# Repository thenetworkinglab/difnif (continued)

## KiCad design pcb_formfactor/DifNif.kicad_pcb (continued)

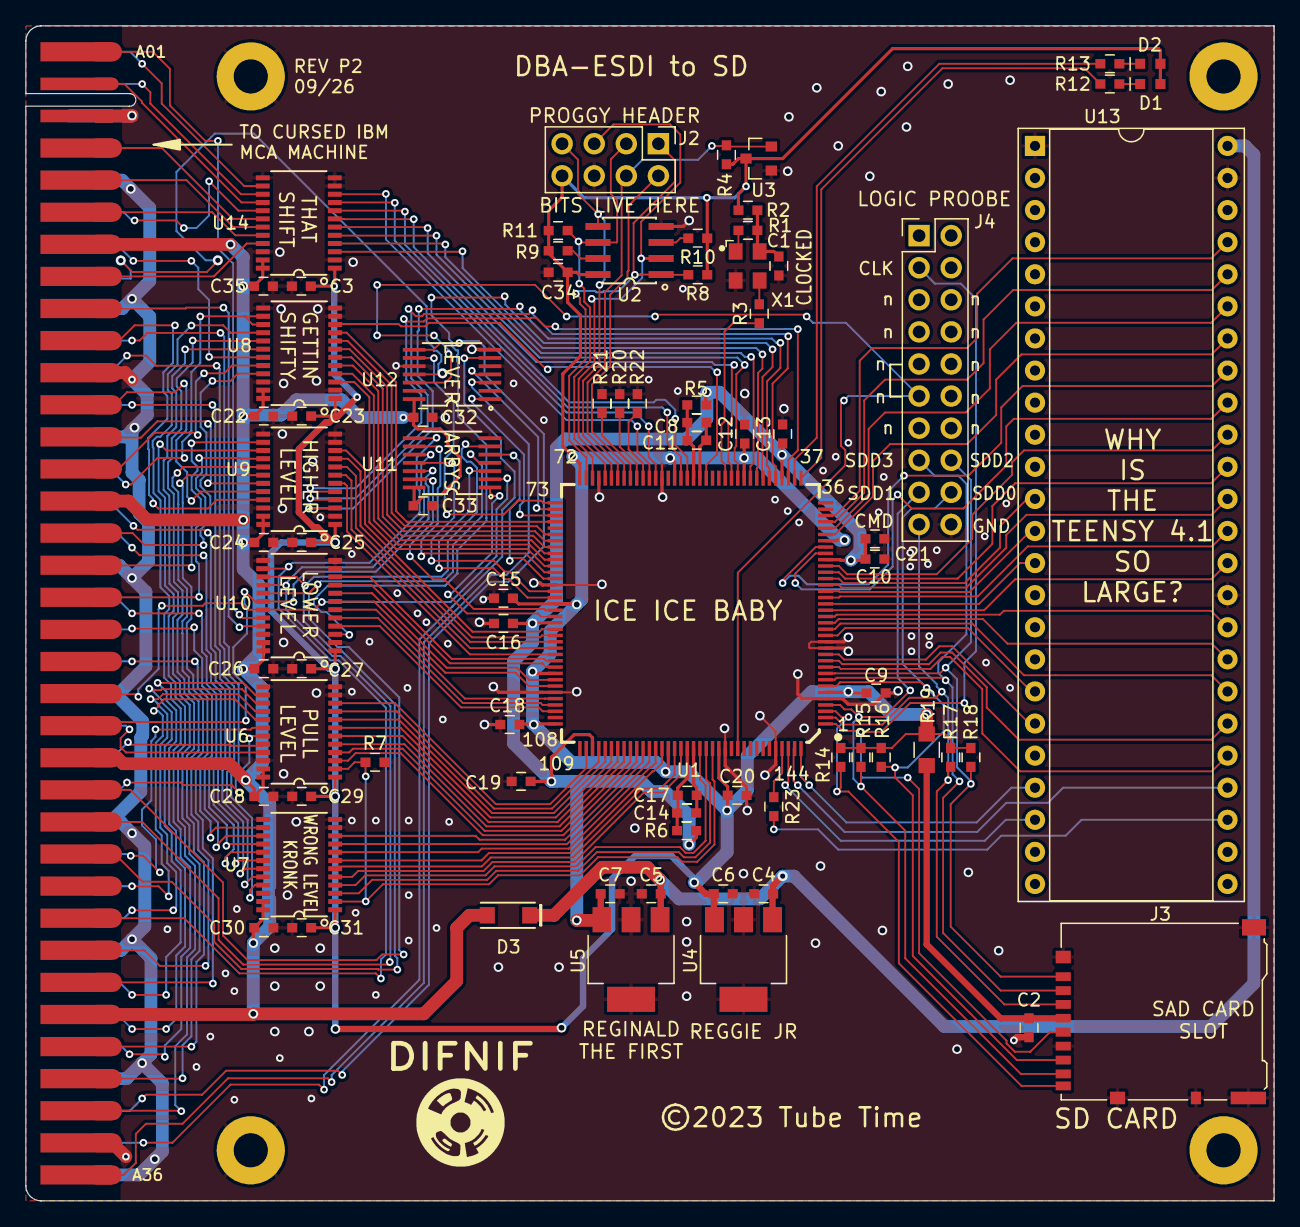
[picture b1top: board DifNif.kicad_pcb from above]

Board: 2 copper layers, 98.8 x 93.0 mm, 84 parts (0 on the bottom side), 172 nets.

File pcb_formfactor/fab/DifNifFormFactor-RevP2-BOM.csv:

Item,Qty,Designators,Manufacturer,Manufacturer Part Number,Description,Value,Footprint,Type,Fitted by,Mouser,Notes
1,13,C1 C2 C9 C10 C11 C12 C13 C15 C16 C17 C18 C19 C34,TDK,CGA3E1X7R1C105AC,Capacitor 1u 0603,1u,CAPC1608X100,SMD,Assembler,810-CGA3E1X7R1C105AC,
2,14,C3 C22 C23 C24 C25 C26 C27 C28 C29 C30 C31 C32 C33 C35,Samsung Electro-Mechanics,CL10B104KB8NNNC,Capacitor 0.1uF 0603,0.1uF,CAPC1608X100,SMD,Assembler,,Any 0.1 uF X7R 0603 rated 16 V or more is fine
3,8,C4 C5 C6 C7 C8 C14 C20 C21,Samsung Electro-Mechanics,CL10A475KP8NNNC,Capacitor 4.7u 0603,4.7u,CAPC1608X100,SMD,Assembler,187-CL10A475KP8NNNC,
4,2,D1 D2,,,"LED, 0603",LED,LEDM1608X50,SMD,Assembler,,Any 0603 LED (e.g. green); 470 ohm from 3.3 V
5,1,D3,Nexperia,PMEG10010ELRX,"Schottky diode 1 A 100 V, SOD-123F",PMEG10010ELR,SOD3716X117,SMD,Assembler,771-PMEG10010ELRX,
6,1,J3,Hirose,DM3AT-SF-PEJM5(40),microSD socket,SDCARD_DM3AT-SF-PEJM5,microSD_HC_Hirose_DM3AT-SF-PEJM5,SMD,Assembler,798-DM3AT-SF-PEJM540,"Check: Mouser code ends in 40, Hirose's packaging variant"
7,6,R1 R4 R8 R9 R10 R11,Yageo,RC0603FR-0710KL,Resistor 10K 0603,10K,RESC1608X55,SMD,Assembler,603-RC0603FR-0710KL,
8,6,R2 R3 R20 R21 R22 R23,Yageo,RC0603FR-0710RL,Resistor 10 0603,10,RESC1608X55,SMD,Assembler,603-RC0603FR-0710RL,
9,2,R5 R6,Yageo,RC0603FR-07100RL,Resistor 100 0603,100,RESC1608X55,SMD,Assembler,603-RC0603FR-07100RL,
10,1,R7,Yageo,RC0603FR-071KL,Resistor 1K 0603,1K,RESC1608X55,SMD,Assembler,603-RC0603FR-071KL,
11,2,R12 R13,Yageo,RC0603FR-07470RL,Resistor 470 0603,470,RESC1608X55,SMD,Assembler,603-RC0603FR-07470RL,
12,5,R14 R15 R16 R17 R18,Yageo,RC0603FR-0747KL,Resistor 47K 0603,47K,RESC1608X55,SMD,Assembler,603-RC0603FR-0747KL,
13,1,R19,Yageo,RC0805FR-070RL,Resistor 0 0805,0,RESC2012X55,SMD,Assembler,603-RC0805FR-070RL,
14,1,U1,Lattice Semiconductor,ICE40HX4K-TQ144,"FPGA, iCE40 HX4K, TQFP-144",ICE40HX4K-TQ144,TSQFP50P2200X2200X160-144,SMD,Assembler,842-ICE40HX4K-TQ144,
15,1,U2,Microchip Technology,SST26VF080A-104I/SN,"SPI flash 8 Mbit, SOIC-8 (FPGA configuration)",SST26VF080A-104I/SN,SOP127P620X175-8,SMD,Assembler,579-26VF080A-104I/SN,
16,1,U3,Diodes Incorporated,APX803S00-29SA-7,"Reset supervisor 2.93 V, SOT-23",APX803S00-29SA-7,SOT95P230X117-3,SMD,Assembler,621-APX803S00-29SA-7,
17,1,U4,Diodes Incorporated,AP2114HA-3.3TRG1,"LDO 3.3 V, SOT-223",AP2114HA-3.3,SOT230P700X170-3,SMD,Assembler,621-AP2114HA-3.3TRG1,
18,1,U5,Diodes Incorporated,AP2114HA-1.2TRG1,"LDO 1.2 V, SOT-223",AP2114HA-1.2,SOT230P700X170-3,SMD,Assembler,621-AP2114HA-1.2TRG1,
19,6,U6 U7 U8 U9 U10 U14,Texas Instruments,SN74LVC8T245PWR,"Dual-supply octal transceiver, TSSOP-24",74LVC8T245,TSOP65P640X120-24,SMD,Assembler,595-SN74LVC8T245PWR,
20,1,U11,Toshiba,74LCX07FT,"Hex open-drain buffer, TSSOP-14",74LCX07,TSOP65P640X110-14,SMD,Assembler,757-74LCX07FTAE,Check: Mouser code adds a packaging suffix (AE)
21,1,U12,Toshiba,74VHCT125AFT,"Quad tri-state buffer, TSSOP-14",74VHCT125,TSOP65P640X110-14,SMD,Assembler,757-74VHCT125AFT,
22,1,X1,ECS Inc.,ECS-2333-100-BN-TR,Oscillator 10 MHz,ASE-xxxMHz,XTAL320X250X120-4,SMD,Assembler,520-ECS-2333-100-BNT,"Check: 10 MHz 3.3 V oscillator, 3.2 x 2.5 mm; Mouser code drops the -TR punctuation"
23,1,J2,,,"2x4 pin header, 2.54 mm",PROG,PinHeader_2x04_P2.54mm_Vertical,THT,Customer,,FPGA flash programming header
24,1,J4,,,"2x10 pin header, 2.54 mm",HPLA_PORT,PinHeader_2x10_P2.54mm_Vertical,THT,Customer,,Logic analyzer header (HP pod)
25,1,U13,,,"2x 1x24 female socket strips, 2.54 mm, rows 15.24 mm apart",Teensy4_1,DIP-48_W15.24mm_Socket,THT,Customer,,Socket for the Teensy 4.1 (Teensy fitted separately)

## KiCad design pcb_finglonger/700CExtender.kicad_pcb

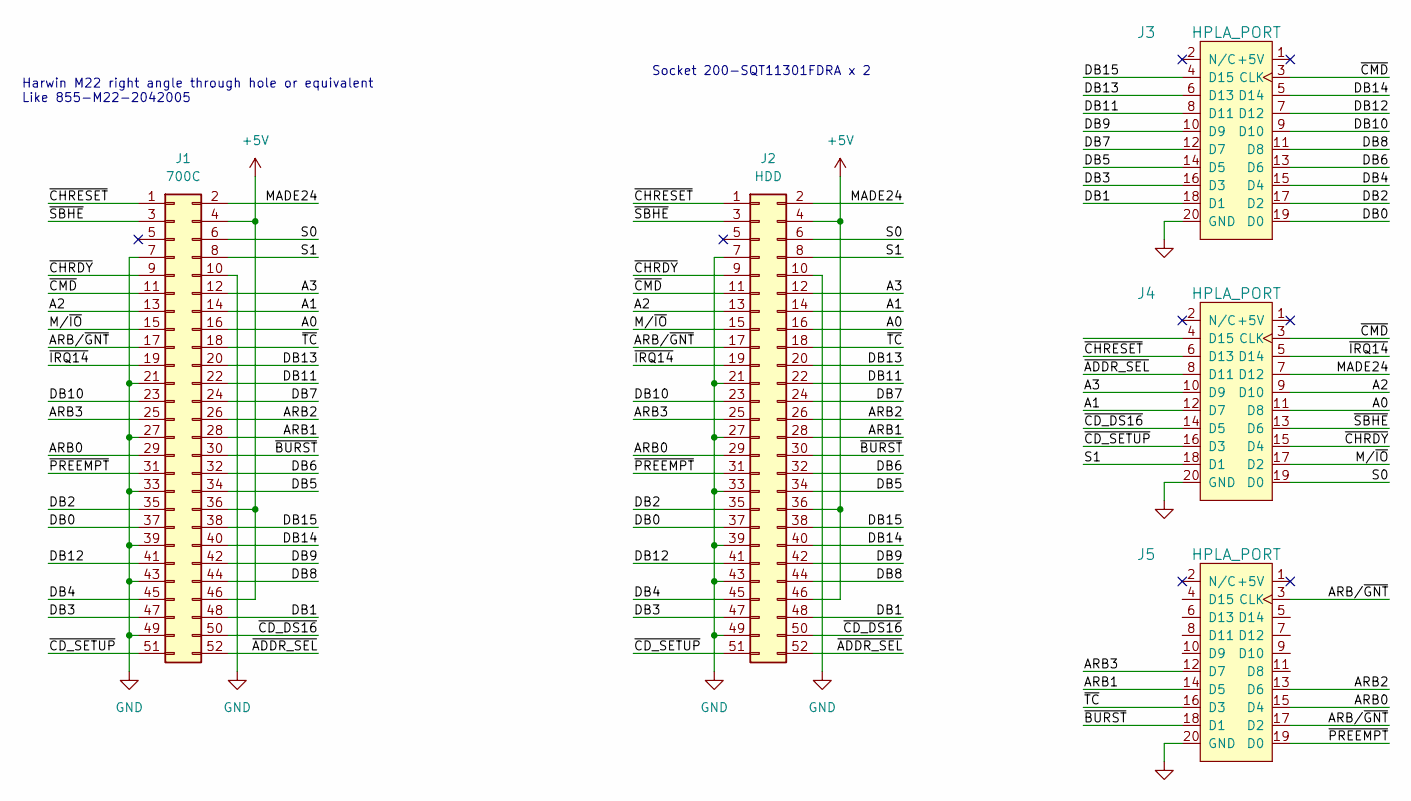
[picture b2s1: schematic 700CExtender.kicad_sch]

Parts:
J1: 700C; PinHeader_2x26_P2.00mm_Vertical
J2: HDD; PinSocket_2x26_P2.00mm_Vertical
J3, J4, J5: HPLA_PORT; PinHeader_2x10_P2.54mm_Vertical

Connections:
+5V: J1.4, J1.36, J1.46, J2.4, J2.36, J2.46
/A0: J1.16, J2.16, J4.11 (D8)
/A1: J1.14, J2.14, J4.12 (D7)
/A2: J1.13, J2.13, J4.9 (D10)
/A3: J1.12, J2.12, J4.10 (D9)
/ARB0: J1.29, J2.29, J5.15 (D4)
/ARB1: J1.28, J2.28, J5.14 (D5)
/ARB2: J1.26, J2.26, J5.13 (D6)
/ARB3: J1.25, J2.25, J5.12 (D7)
/ARB/~GNT: J1.17, J2.17, J5.3 (CLK), J5.17 (D2)
/DB0: J1.37, J2.37, J3.19 (D0)
/DB1: J1.48, J2.48, J3.18 (D1)
/DB2: J1.35, J2.35, J3.17 (D2)
/DB3: J1.47, J2.47, J3.16 (D3)
/DB4: J1.45, J2.45, J3.15 (D4)
/DB5: J1.34, J2.34, J3.14 (D5)
/DB6: J1.32, J2.32, J3.13 (D6)
/DB7: J1.24, J2.24, J3.12 (D7)
/DB8: J1.44, J2.44, J3.11 (D8)
/DB9: J1.42, J2.42, J3.10 (D9)
/DB10: J1.23, J2.23, J3.9 (D10)
/DB11: J1.22, J2.22, J3.8 (D11)
/DB12: J1.41, J2.41, J3.7 (D12)
/DB13: J1.20, J2.20, J3.6 (D13)
/DB14: J1.40, J2.40, J3.5 (D14)
/DB15: J1.38, J2.38, J3.4 (D15)
/MADE24: J1.2, J2.2, J4.7 (D12)
/M/~IO: J1.15, J2.15, J4.17 (D2)
/S0: J1.6, J2.6, J4.19 (D0)
/S1: J1.8, J2.8, J4.18 (D1)
/~ADDR_SEL: J1.52, J2.52, J4.8 (D11)
/~BURST: J1.30, J2.30, J5.18 (D1)
/~CD_DS16: J1.50, J2.50, J4.14 (D5)
/~CD_SETUP: J1.51, J2.51, J4.16 (D3)
/~CHRDY: J1.9, J2.9, J4.15 (D4)
/~CHRESET: J1.1, J2.1, J4.6 (D13)
/~CMD: J1.11, J2.11, J3.3 (CLK), J4.3 (CLK)
/~IRQ14: J1.19, J2.19, J4.5 (D14)
/~PREEMPT: J1.31, J2.31, J5.19 (D0)
/~SBHE: J1.3, J2.3, J4.13 (D6)
/~TC: J1.18, J2.18, J5.16 (D3)
GND: J1.7, J1.10, J1.21, J1.27, J1.33, J1.39, J1.43, J1.49, J2.7, J2.10, J2.21, J2.27, J2.33, J2.39, J2.43, J2.49, J3.20 (GND), J4.20 (GND), J5.20 (GND)

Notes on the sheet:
Harwin M22 right angle through hole or equivalent Like 855-M22-2042005
Socket 200-SQT11301FDRA x 2

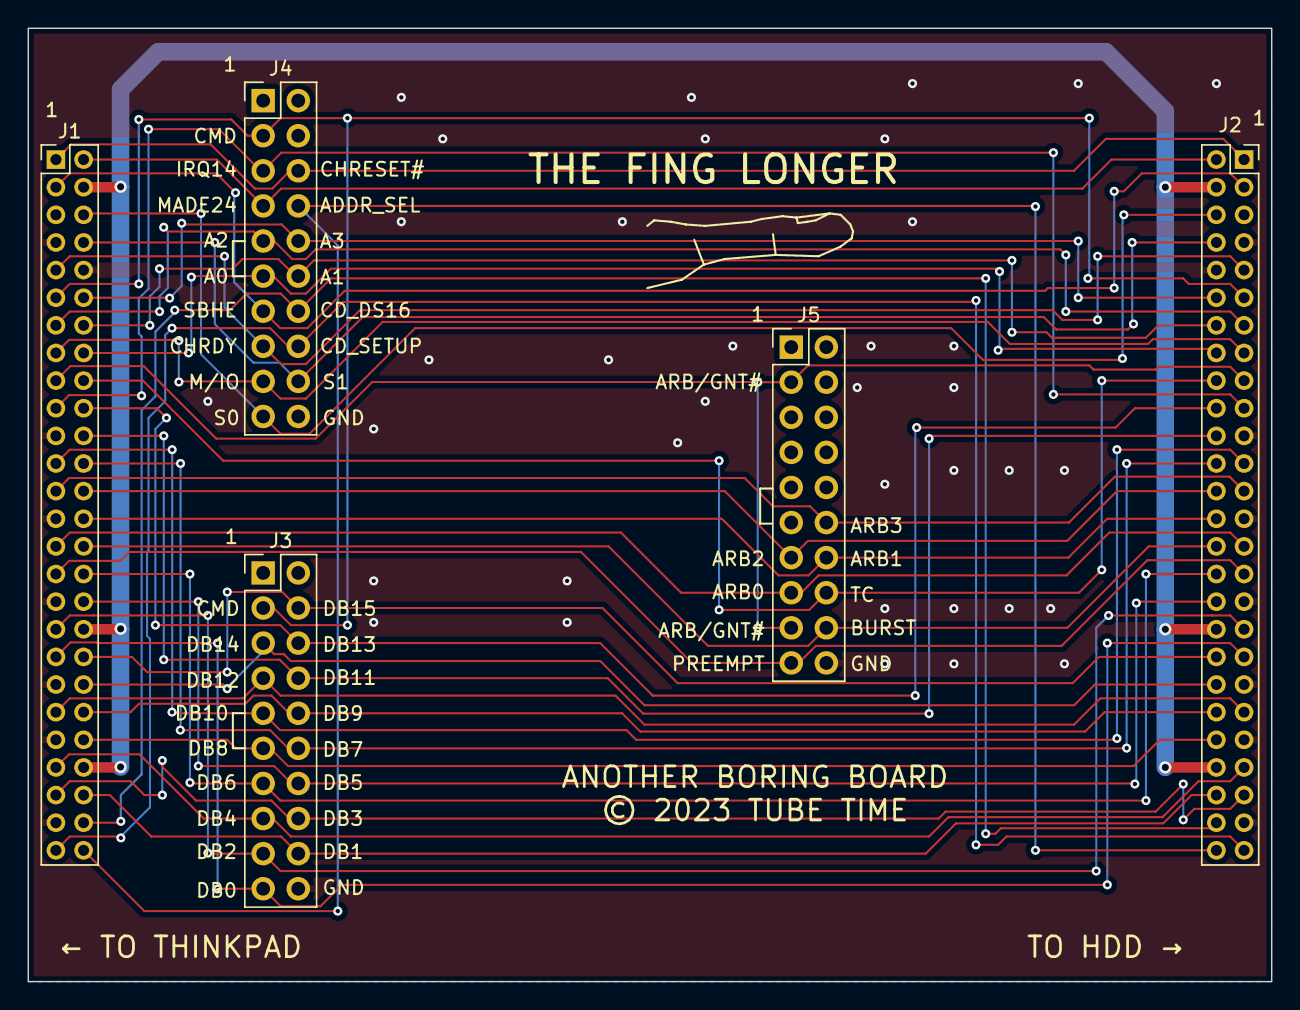
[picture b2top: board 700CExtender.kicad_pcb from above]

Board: 2 copper layers, 90.0 x 69.0 mm, 5 parts (0 on the bottom side), 42 nets.

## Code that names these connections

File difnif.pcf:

### icetest

### Copyright (c) 2021 Eric Schlaepfer
### This work is licensed under the Creative Commons Attribution-ShareAlike 4.0
### International License. To view a copy of this license, visit
### http://creativecommons.org/license/by-sa/4.0/ or send a letter to Creative
### Commons, PO Box 1866, Mountain View, CA 94042, USA.

### Clock
set_io clk_10m      49

### Micro Channel bus
set_io chreset_l    52 # Probably not actually chreset_l!

set_io cd_ds16_l    73
set_io irq14_l      74
set_io cd_chrdy_l   75
set_io chreset      76
set_io sbhe_l       78
set_io s0_w_l       79
set_io s1_r_l       80
set_io cmd_l        81
set_io bus_a[3]     82
set_io bus_a[2]     83
set_io arb_o[3]     84
set_io arb_o[2]     85
set_io arb_o[1]     87
set_io arb_o[0]     88
set_io burst_o_l    90
set_io preempt_o_l  91
set_io bus_a[1]     93
set_io m_io_l       94
set_io bus_a[0]     95
set_io arb_gnt_l    96
set_io tc_l         97
set_io arb[3]       98
set_io arb[2]       99
set_io arb[1]       101
set_io arb[0]       102
set_io burst_l      104
set_io preempt_l    105
set_io cd_setup_l   106
set_io addr_sel_l   107
set_io bus_d[13]    110
set_io bus_d[11]    112
set_io bus_d[10]    113
set_io bus_d[7]     114
set_io bus_d[6]     115
set_io bus_d[5]     116
set_io bus_d[2]     117
set_io bus_d[0]     118
set_io bus_d[15]    119
set_io bus_d[14]    120
set_io bus_d[12]    121
set_io bus_d[9]     122
set_io bus_d[8]     124
set_io bus_d[4]     125
set_io bus_d[3]     128
set_io bus_d[1]     129
set_io data_dir     130


### Teensy connections
# Data port (bidirectional)
set_io tn_d[0]      29
set_io tn_d[1]      28
set_io tn_d[2]      21
set_io tn_d[3]      23
set_io tn_d[4]      17
set_io tn_d[5]      18
set_io tn_d[6]      26
set_io tn_d[7]      25
set_io tn_d[8]      33
set_io tn_d[9]      34
set_io tn_d[10]     31
set_io tn_d[11]     32
set_io tn_d[12]     11
set_io tn_d[13]     16
set_io tn_d[14]     15
set_io tn_d[15]     12

# Address pins
set_io tn_addr[0]   24
set_io tn_addr[1]   20
set_io tn_addr[2]   22
set_io tn_addr[3]   19

# Control pins
set_io tn_rd        143
set_io tn_wr        10
set_io tn_int       144

# Spares
set_io tn35         141
set_io tn30         142

### LEDs
set_io led0         37
set_io led1         38

### SD card
set_io sd_clk       1
set_io sd_cmd       2
set_io sd_switch    3
set_io sd_d[1]      4
set_io sd_d[0]      7
set_io sd_d[3]      8
set_io sd_d[2]      9

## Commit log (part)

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2023-07-29 Initial version
2023-07-29 Updated PCF
2023-07-29 PCF mods, add first test bench
2023-07-29 Fix test bench issues
2023-07-29 Add a few files to gitignore
2023-08-01 Start of basic read transfer
2023-08-10 last checkin for sync mode
2023-08-10 async implementation
2023-08-15 add data byte steering
2023-08-15 16-bit transfers in test bench
2023-08-16 fix burst_o_l being held low
2023-08-18 remove made24, add chreset
2023-08-18 refactoring
2023-08-18 start implementing flags
2023-08-23 initial teensy port
2023-08-23 add teensy sketch and interface with test reg
2023-08-23 gitignore update
2023-08-30 register access from MCA to Teensy works!
2023-09-03 added ISR reg
2023-09-04 MCA bus highlighting for gtkwave
2023-09-04 add cifr and sifr
2023-09-04 add flag bits and interrupt
2023-09-04 implement some command structure
2023-09-23 Hook up interrupt output
2023-09-24 improve host interface
2023-09-24 get rid of extra pending flag. add some tests.
2023-09-24 fix SIFR mailbox glitches
2023-09-24 hardware triggered busy bit
2023-09-26 fix ATN mailbox
2023-09-26 ISR mailbox fixes
2023-09-26 fix CIFR double read issue
2023-09-27 add data register and tranfer request flag
2023-09-28 attach buffer cmds and read sector!
2023-09-29 add clear flag function
2023-09-29 fix interrupt behavior
2023-09-29 add POS information cmd, POS regs
2023-09-30 initial (broken) dma
    Read DMA sometimes works. Write DMA freezes the machine.
2023-10-03 fix la_dma_selected holding too long during write dma cycle
2023-10-04 DMA (non burst) working.
2023-10-05 add hard reset. code cleanup.
2023-10-05 Add most remaining commands
2023-10-07 read-only disk image support
2023-10-07 Enable POS registers
2023-10-07 Pseudo RBA, log spurious EOI
2023-10-08 Implemented pseudo RBAs. It boots now!
2023-10-08 stubbed out write routine
2023-10-17 Add 1C cmd variant. Fix write off-by-two error
2023-10-17 test output for ATN flag testing
2023-10-19 fix atn flag clock domain crossing issue
2023-10-19 fix SIFR and CIFR mailbox issues
2023-10-19 data register flag tidy up
2023-10-20 speedup Teensy to FPGA interface
2023-10-20 Add synch clock line to Teensy interface
2023-11-10 Enable standalone operation
2023-11-10 Rearrange verilog location
2023-11-10 Add PCB files
2023-11-10 add initial difdiag
2023-11-11 Added 72-pin form factor board
2023-11-11 Add diode OR, add clock series R
2023-11-28 fix non-POS IO when card disabled. test bench tweaks
2023-11-28 fix rare dma glitch
2023-11-28 fabout form factor pcb
2023-12-02 Support 72-pin form factor
2023-12-17 potential fix for bad sector writes
2023-12-17 difdiag: add int13h tests
2026-01-27 add POS bypass mode
2026-01-27 Readme, docs, update license
2026-01-27 Bug list
